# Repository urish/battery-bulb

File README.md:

# battery-bulb

Battery Powered Magic Blue Bulb - Charging + Power Supply module

Learn more about it in my blog post - [How To Make Your Very Own Wireless, Extra-Magic Smart Bulb](https://medium.com/@urish/how-to-make-your-very-own-wireless-extra-magic-smart-bulb-bb40b4e3a726).

## Bill of Materials

| Name | Quantity | Unit Price | Link | Comment |
|-------------------------------------|----------|-------|---------------------------------------------------------------------------------------------------------------------------------------------------------------------|--------------------|
| 12V Step-Up Voltage Regulator | 1 | $3.95 | [Pololu](https://www.pololu.com/product/2117) | |
| MicroUSB Connector | 1 | $1.50 | [SparkFun](https://www.sparkfun.com/products/8533) |  |
| SMD Right Angle Switch | 1 | $0.95 | [SparkFun](https://www.sparkfun.com/products/10860) |  |
| 2-Pin JST Connector | 1 | $0.95 | [SparkFun](https://www.sparkfun.com/products/9914) | LiPo Battery Connector |
| MCP73831T | 1 | $0.15 | [AliExpress](https://www.aliexpress.com/item/10PCS-MCP73831T-2ACI-OT-SOT23-5-MCP73831T-2ACI-SOT-MCP73831T-MCP73831-SMD-free-shipping/32714249253.html) | LiPo Charging Chip  |
| RT9013-33GB | 1 | $0.19 | [AliExpress](https://www.aliexpress.com/item/RT9013-33GB-RT9013-33PB-3-3V-SOT23-5-imports-Original-New-NFTXKJ/32467674180.html) | 3.3V Voltage Regulator |
| 0603 4.7kΩ Resistor | 1 | $0.01 | - | R3 |
| 0603 10kΩ Resistor | 1 | $0.01 | - |  R2 |
| 0603 LED | 1 | $0.01 | -  | Charging indicator |
| 0603 4.7uF Capacitor | 2 | $0.01 | - | C1, C2

In addition, you will also need a small LiPo battery - a [100mAH](https://www.adafruit.com/product/1570) battery should do the trick, and obviously, [the bulb itself](https://www.gearbest.com/smart-light-bulb/pp_230349.html).

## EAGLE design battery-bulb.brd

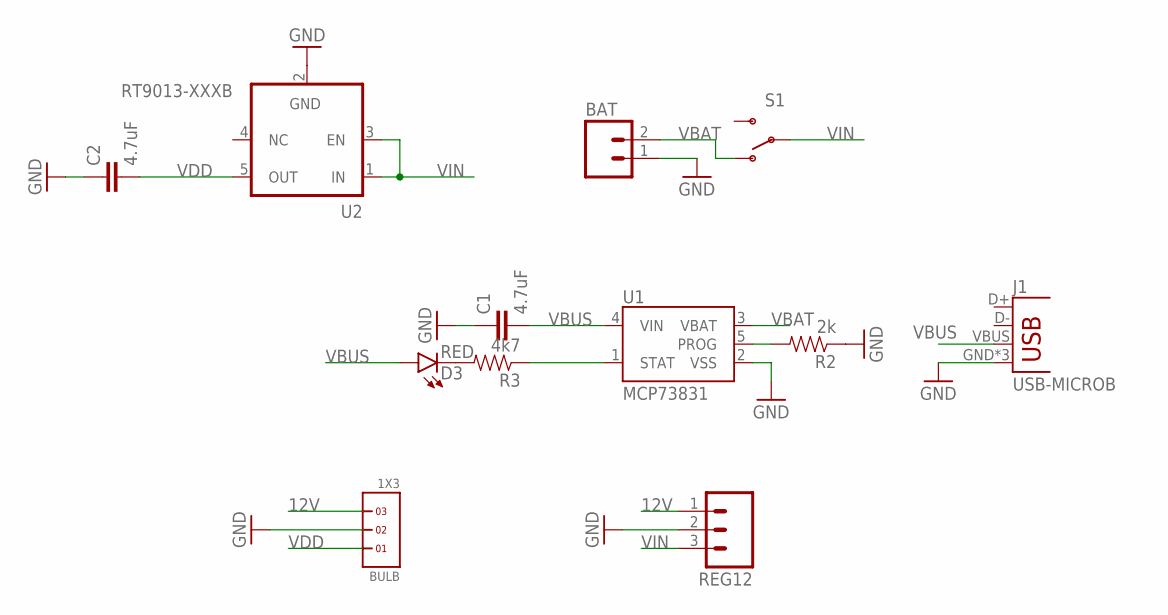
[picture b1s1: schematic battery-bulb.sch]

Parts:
BAT: M02JST-PTH-2; JST-2-PTH
BULB: 1X3
C1, C2: 4.7uF; 0603-CAP
D3: RED; LED-0603
J1: USB-MICROB
R2: 2k; 0603-RES
R3: 4k7; 0603-RES
REG12: M03LOCK; 1X03_LOCK
S1: SWITCH-SPDT-SMD-A; SWITCH-SPST-SMD-A
U1: MCP73831; SOT23-5
U2: RT9013-XXXB; SOT23-5

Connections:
12V: BULB.3, REG12.1
GND: BAT.1, BULB.2, C1.1, C2.1, J1.GND, J1.MT1 (GND), J1.MT2 (GND), R2.1, REG12.2, U1.2 (VSS), U2.2 (GND)
unnamed: R2.2, U1.5 (PROG)
unnamed: R3.1, U1.1 (STAT)
unnamed: D3.C, R3.2
VBAT: BAT.2, S1.1 (O), U1.3 (VBAT)
VBUS: C1.2, D3.A, J1.VBUS, U1.4 (VIN)
VDD: BULB.1, C2.2, U2.5 (OUT)
VIN: REG12.3, S1.2, U2.1 (IN), U2.3 (EN)

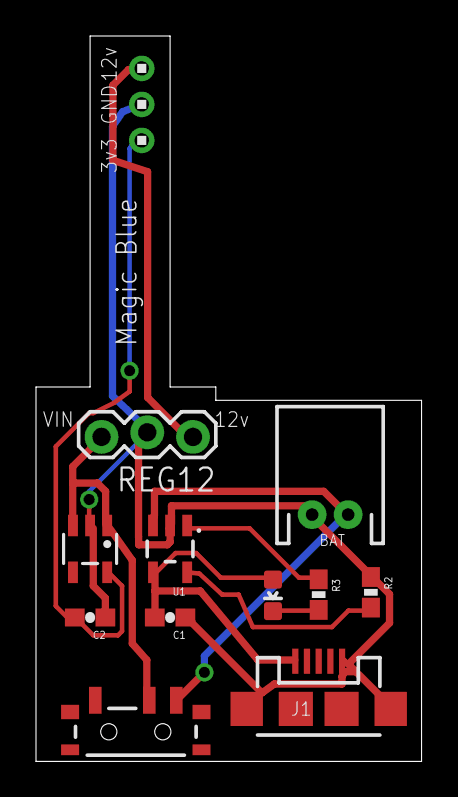
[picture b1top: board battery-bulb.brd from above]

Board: 2 copper layers, 21.4 x 40.3 mm, 12 parts (0 on the bottom side), 9 nets.

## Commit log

2017-05-08 doc: link to blog post
2017-05-08 doc: add image
2017-05-23 board revision 2
    extend the board with direct connection to the bulb's logic board
2018-08-25 docs: update BOM
    add 12V step-up, and link to battery / bulb

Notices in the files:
parts and their libraries:
SparkFun-Connectors: Licensing: Creative Commons ShareAlike 4.0 International - https://creativecommons.org/licenses/by-sa/4.0
